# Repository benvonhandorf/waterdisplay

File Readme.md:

# Overview

Water Display is intended to be an open source project combining electronics, embedded software and water to create a small water display for our small pond.

# Project goals

As with any project, there are multiple goals here, both primary and secondary

## Primary
* Functional, programmable water display.
* Further my knowledge of electronics.
* Gain some experience circuit board design, using KiCad.

## Secondary
* Minimize cost.  In particular, cost per node should be kept as low as possible.
* Maximize flexibility.  Creating an extensible design capable of doing other tasks in the future would be optimal.
* Learn a new microcontroller, if the opportunity presents itself.

# Design Philosophy

The goal is to have multiple small independent water squirters (a _node_) located around the pond.  Each of these will contain:
* (A small 12V solenoid)[https://www.sciplus.com/p/12-VDC-SOLENOID-VALVE-10PACK-SAVINGS_54414]
* RGB LED
  * WS2812 seems likely
  * APA102 would also work and we have no shortage of GPIO in the node (see below)

These will be run from a central controller running various patterns which could be based on sensors or some other option.

# Component selection

## General

As part of the goal to do circuit board design, most components will be sourced as SMD, where possible.  A few power components will be through hole (e.g. MOSFET, flyback diode) just to give a ridiculous amount of rating overhead.

## Node design

After consideration, I've decided to pursue making each node smart.  This minimizes the required bus lines, maximizes the expandability of the installation and hopefully allows for different use cases for the electronic work.

Intended communication is over a shared serial UART from the controller to all nodes.  Each node will have an address assigned to it (compiled in to the flash) and the protocol will allow it to only process messages intended for it.

To further reduce cabling requirements, each node will have a local 5V regulator for Vdd supply for the microcontroller and RGB LED.

### Microcontroller

General Requirements:
* UART
* 5V part (to eliminate the need for further regulation)
* At least 3 GPIO pins
  * MOSFET
  * LED Data
  * LED Clock, if an APA102 style RGB LED is used

In order to keep cost per part down and given the very modest requirements above, an STM8 type part is recommended.  Research indicates they can be sourced at less than $0.50/pc in small quantities.  Given the small amount of board space available (with an optimally sized circuit board) and the need to hand-solder the parts, a TSSOP20 part is suggested.  RAM and Flash requirements should be very modest, to a STM8S003F or similar part should be sufficient in all respects.  Even if I decided to make a 4-way node, there should still be sufficient GPIO available.

Given the lack of additional requirements, where possible GPIO pins should be selected to maximize future expandability.  SPI and I2C should be left available, if possible, along with ADC pins.  

#### Microcontroller supporting parts

* 1 uF ceramic capacitor - Power smoothing Capacitor 
* Cext - 1 uf
  * 0.3 Ohm Max ESR at 1MHz 
  * 15 nH Max ESL at 1MHz
* If an external oscillator is necessary:
  * 16 MHz crystal
  * 2 x 20pF Load capacitors, depending on Cload

### Connectivity

Connections from central node are:
* +12V DC
* 0V DC
* Serial Data (TX from controller)
* Pressurized water (obviously.  Solenoid ratings call for < 4psi)

Additional local connections for programming and debugging (not exposed through weatherproof casing)
* Serial Data (TX from node)
* Reset
* SWIM
* +5VDC
* Ground

### Additional

In order to make the design as maintainable as possible, the following indicator LEDs will be placed on the board as well:
* Green power indicator LED, connected to 12V line
* Red "active" LED, connected to MOSFET control pin

# BOM
## Per Node BOM
* Microcontroller
  * STM8S003F ~ $0.50/pc
  * STM8S103F ~ $0.50/pc
  * MSP430G2001 ~ $0.
* AMS1117 ~ $0.10/pc
* 2x female spade connectors ~ $0.28/pc (e.g. 1217080-1)[http://www.newark.com/webapp/wcs/stores/servlet/ProductDisplay?catalogId=15003&langId=-1&urlRequestType=Base&partNumber=30H5445&storeId=10194]
*

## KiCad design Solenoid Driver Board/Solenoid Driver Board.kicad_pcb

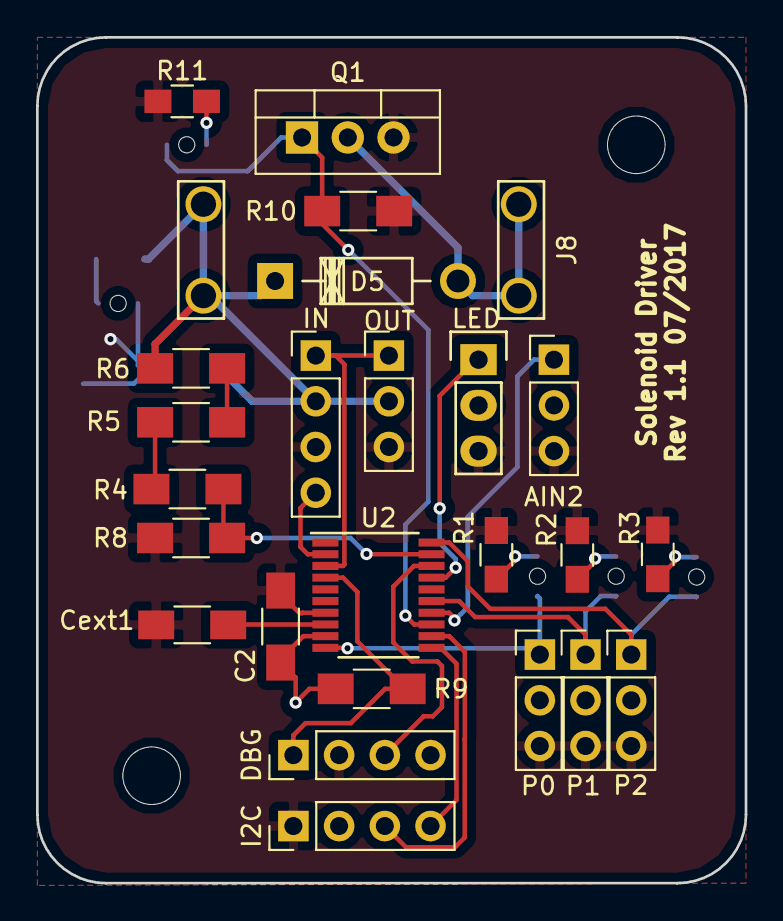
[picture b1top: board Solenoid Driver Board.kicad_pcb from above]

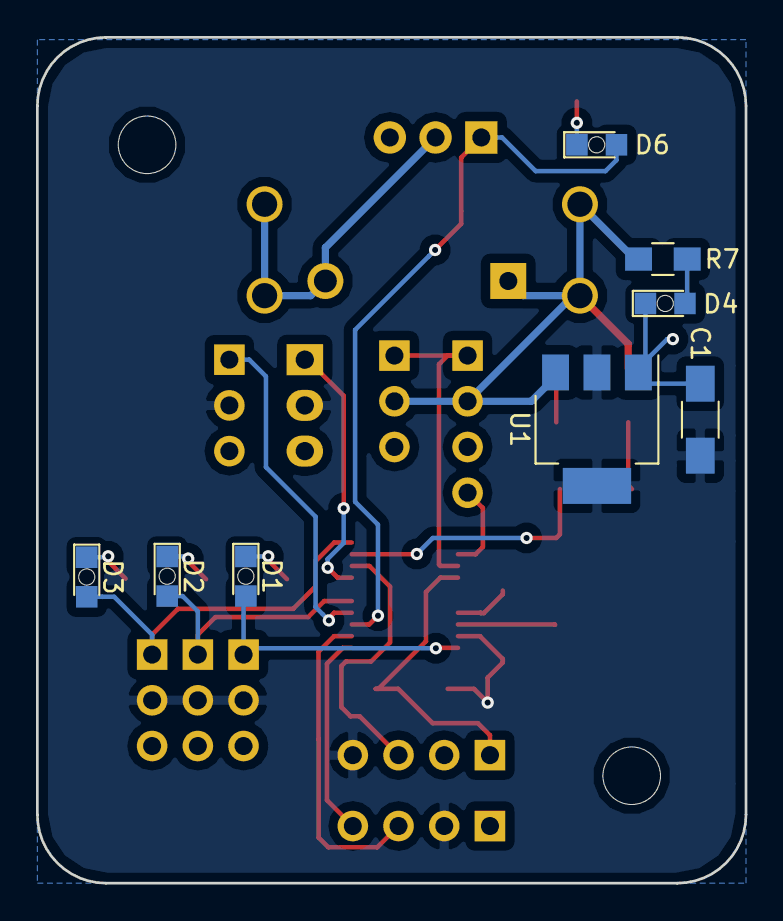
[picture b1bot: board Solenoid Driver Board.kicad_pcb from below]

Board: 2 copper layers, 39.4 x 47.0 mm, 33 parts (8 on the bottom side), 25 nets.

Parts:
AIN2: AIN2; Pin_Header_Straight_1x03_Pitch2.54mm
C1: 1 uF; C_1206_HandSoldering
C2: 100nf; C_1206_HandSoldering
Cext1: 1 uF; C_1206_HandSoldering
D1, D2, D3, D6: ON; LED_0805_Bottom_Hole
D4: PWR; LED_0805_Bottom_Hole
D5: 1N4007; Diode_DO-41_SOD81_Horizontal_RM10
DBG: DEBUG; Pin_Header_Straight_1x04_Pitch2.54mm
I2C: I2C; Pin_Header_Straight_1x04_Pitch2.54mm
IN: BUS-I; Pin_Header_Straight_1x04_Pitch2.54mm
J8: Solenoid; Spade_Conn_Solenoid
LED: RGB_LED; Pin_Header_Straight_1x03
OUT: BUS-O; Pin_Header_Straight_1x03_Pitch2.54mm
P0: CH1; Pin_Header_Straight_1x03_Pitch2.54mm
P1: CH2; Pin_Header_Straight_1x03_Pitch2.54mm
P2: CH3; Pin_Header_Straight_1x03_Pitch2.54mm
Q1: IRLB8721PBF; TO-220_Vertical
R1, R2, R3, R11: 330; R_0805_HandSoldering
R4, R5, R6, R8, R9: 10k; R_1206_HandSoldering
R7: 1k; R_0805_HandSoldering
R10: 10K; R_1206_HandSoldering
U1: AMS1117-5.0; SOT-223
U2: STM8S003F3P; TSSOP-20_4.4x6.5mm_Pitch0.65mm

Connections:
+5V: AIN2.2, C1.1, C2.1, DBG.4, I2C.2, LED.2, P0.2, P1.2, P2.2, R9.1, U1.2, U1.4, U2.9
+12V: D5.1, IN.2, J8.1, OUT.2, R6.1, R7.1, U1.3
AIN2: AIN2.1, U2.14
CH0: D1.2, P0.1, U2.10
CH1: D2.2, P1.1, U2.15
CH2: D3.2, P2.1, U2.20
GND: AIN2.3, C1.2, C2.2, Cext1.2, D4.1, DBG.2, I2C.1, IN.3, LED.3, OUT.3, P0.3, P1.3, P2.3, Q1.3, R1.1, R2.1, R3.1, R8.1, R10.1, R11.1, U1.1, U2.7
NRST: DBG.1, R9.2, U2.4
unnamed: Cext1.1, U2.8
unnamed: D1.1, R1.2
unnamed: D2.1, R2.2
unnamed: D3.1, R3.2
unnamed: D4.2, R7.2
unnamed: D5.2, J8.2, Q1.2
unnamed: D6.1, R11.2
unnamed: LED.1, U2.17
unnamed: R4.1, R5.1
unnamed: R5.2, R6.2
PC3: D6.2, Q1.1, R10.2, U2.13
RX: IN.1, OUT.1, U2.3
SCL: I2C.3, U2.12
SDA: I2C.4, U2.11
SWIM: DBG.3, U2.18
TX: IN.4, U2.2
VIN_A: R4.2, R8.2, U2.19

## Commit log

2015-03-02 Source for solenoid tests
2015-03-02 Added initial part designs
2015-03-05 Added support for a compact layout, where alternate solenoids are displaced Y axis.
    + Still possible to make it more compact (along X) by rotating so that feed tubes are on alternating sides.
2015-03-15 Fixed bug in iteration, added pattern to pinout array
2017-04-17 Old changes
2017-04-18 Restarting the repo
2017-04-18 Documentation work
2017-04-18 Cleaned old designs
2017-04-18 Initial schematic work
2017-04-18 Spade connectors added
2017-04-30 PCB Design completed and apparently acceptable
2017-05-07 Initial thoughts on protocol. Initial board redesign notes. Added libraries for firmware development
2017-05-07 Added oshpark renders of v1.0 of board
2017-05-14 Basic python simulation framework for display creation
2017-05-14 Added support for fade and off commands
2017-05-15 Added pond outline
2017-05-21 Firmware framework, makefile, board_bring_up tests started
2017-05-21 Circular buffer work for UART
2017-05-21 removing object files
2017-05-21 Circular buffer tests passing, starting work on UART TX code
2017-05-22 UART TX and RX working for basic cases. Still can't stream data to the TX too quickly
2017-05-22 Clean up some debugging
2017-05-23 Protocol changes to deal with possible RGBW LEDs, framework for controller and pl9823
2017-05-27 pl9823 work
2017-05-27 pl9823 working with brute force
2017-05-27 Basic LED fading, not correct yet
2017-05-27 Added unit tests for pl9823 driver
2017-05-27 Refactored hardware PL9823 logic out of general LED driver.
2017-05-27 Fixed LED stand write routine
2017-05-28 Added LED write and fade interface
2017-05-28 Controller test started, main loop refined
2017-05-28 Controller tests complete and passing
2017-05-29 Timer code started but not yet working, UART changed to use address mode
2017-05-29 Merged
2017-05-29 Clearing timer UIE bit made timer work
2017-05-29 Repair the main loop back to fully functional state
2017-05-29 led driver debugging
2017-05-29 Fix bug with led_driver not initting pl9823_driver (mega-DUH)
2017-05-29 Removed python virtual environment from repo
2017-05-29 Working on comms
2017-05-30 Python code working, address handling on node working
2017-05-31 Debugging LED fading issues
2017-05-31 Fixed fading bug
2017-05-31 Added headless version of program runner
2017-06-01 Headless program working
2017-06-01 Enhanced debugging on dump
2017-06-02 Fix reporting of fade colors
2017-06-02 Fix tabs
2017-06-08 Added address configuration to controller and eeprom handling
2017-06-10 Script to set address on nodes
2017-06-11 Refactor headless to support different display programs. Create an image based display program
2017-06-11 Added launcher script
2017-06-14 Fixing impage parser for use on rpi
2017-06-17 Added ack support
2017-06-17 Additional ack debugging
2017-06-18 Refactored controller to be easier to comprehend
2017-06-18 Simplified display program to crash node more quickly
2017-06-24 Added status drivers, removed batched uart write
2017-06-25 Moved fade to TIM4, started work on new board revision
2017-06-25 Added IWDG timer support
2017-06-26 Layout work begun on v1.1 of PCB
2017-06-26 New source image
2017-07-04 PWM Test, lots of work on v1.1 PCBs
2017-07-04 Launcher and python script changes
2017-08-03 Board rev 1.1
2017-08-15 Reorganized node firmware
2017-08-22 Add option bit configuration to makefiles
2017-08-22 Switch to correct AFR bit
2017-08-22 PWM Working on solenoid board
2017-08-22 PWM driver working, led driver configurable with pound if
2022-07-02 Backup
